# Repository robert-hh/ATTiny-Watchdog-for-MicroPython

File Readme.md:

# ATTiny based Watchdog (for MicroPython devices)

These are two variants of an external watchdog, which I made for use with ES32 based MicroPython
devices. Even if the ESP32 has a built-in watchdog, it is not really reliable. Actually, using
it does not improve the long term reliability of an application.

These two variants consists of two components:

- Software for an AttinyX5 device, which is the actual Watchdog. For (my) convenience
I made it with the Arduino development environment. I selected the ATTiny because it is easy 
available, cheap, well documented, and easy to use and available in various packages. 
Besides the controller and a pull-up resistor for the input, no other component is required.
- A small class for the MicroPython device controlling the watchdog.

These two variants differ on how the communication between the micropython device and
the watchdog is done.

- Pulse: Communication to the watchdog is via one GPIO line and pulses of various duration. 
That is the only drawback of using an external watchdog: it requires an GPIO port for feeding.
- Serial: Communication to the Watchdog is via one GPIO line and serial commands at 9600 baud.
Since only data is sent, I used the RMT module for sending, saving the UART port. For devices
without RMT a UART based variant is supplied.

The run-time overhead of both variants is comparable and differs only in the length of the 
feed pulse. For the **pulse** variant, it is 20µs, for the **serial** and **uart**  variant,
it is 100µs (the length of the start bit at 9600 baud).

Both watchdogs have two states, a sleep state and a watch state. They start in sleep state and have 
to be armed by a dedicated signal. The watch state can be suspended, e.g. before going to deep sleep.
The current consumption of the watchdog is about 1 µA, with short bursts of 1 mA for 500µs every second.

When the watchdog fires (Barks), it creates reset pulse of 100ms duration. For that time, the 
respective GPIO pin of the ATTiny will set to output mode. In all other times, it is in
input mode with pull-up active.

In both version, an Reset signal on the supervized micro is detected and will cause the watchdog 
to enter the sleep state. If the sleep state is timed (see command stop() below), then for that period only.

## Python class

### Serial version, RMT
watchdog = Watchdog(port, status=None, restart=False, baudrate=9600)

**Port** is the name or number of the GPIO port. It is important not to supply a pin
object, but the name, e.g. "P9" or 14. The GPIO pin will be initialized by the class.  
**status** is the name/number of a pin, which, if connected, can be used to read back the 
status of the watchdog. If the status pin is set,   
**restart**=True will cause a feed signal to be sent when status starts toggling,
which is when the watch period is halfway expired. This is useful in situations, when there is no
suitable place for a feed() call. The drawback: feed() is then called in a callback function, which
may even be executed when the to-be-supervized functions stoppped working.
**baudrate** is the speed to be used. The default is 9600 and hardly ever changed.

### Serial version, UART
watchdog = Watchdog(uart, status=None)

**uart** has be be an UART object created with the proper baud rate and pin assignments.  
**status** is a Pin object, defined in input mode for reading back the status pin.

### Pulse version
watchdog = Watchdog(port, status=None, restart=False)

**Port** is the name or number of the GPIO port. It is important not to supply a pin
object, but the name, e.g. "P9" or 14. The GPIO pin will be initialized by the class.  
**status** is the name/number of a pin, which, if connected, can be used to read back 
the status of the watchdog.  
**restart**=True will cause a feed signal to be sent when status starts toggling,
which is when the watch period is halfway expired. This is useful in situations, when there is no
suitable place for a feed() call. The drawback: feed() is then called in a callback function, which
may even be executed when the to-be-supervized functions stoppped working.  

## Methods

### watchdog.start(seconds)

Set the timeout period of the watchdog to seconds and start the watch mode. The granularity is seconds.
The shortest timeout period that can be set in the pulse version is about 15 seconds.

### watchdog.feed()

Feed the dog. The timeout time will be set to the value given by the start() command.
Do not call feed(), e.g. in a different thread, before the start() command terminated, 
which may take a while. After calling feed(), it takes about 2 ms until the status as reported by a
call to status() changes. 

### watchdog.stop(seconds=0)

Suspend the watch state for the given time and enter the sleep state. 
If the value of seconds is not zero, sleep only for that amount of time 
and return to the watch state after that.

### watchdog.status()

Read back the status of the watchdog using the pin set in the constructor. Return values:  

|Value|Meaning|
|:-:|:-|
|0|The watchdog is sleeping|
|1|The watchdog is active. If the watch period is halfway elapsed, the value gets togggling once per second. That can be used for instance to trigger a callback, which feeds the watchdog.|
|None|Port no set|

### watchdog.send(string)

Send string to the watchdog device using the baud rate set in the constructor. 
That is the basic command used by the methods start() and stop(). 
You can use that to toggle DEBUG output from the watchdog, by calling send("D").
In the pulse version, send() exists but does not do anything.

## Command interface of the ATTiny

### Pin assignments of the Attiny:

|Pin|Port|Function|
|:-:|:-:|:-|
|2|PB3|Reset signal to host (required)|
|3|PB4|Feed and command input pin (recommended)|
|4|GND|GND (required)|
|6|PB1|Status pin (optional)|
|7|PB2|Debug output pin. (optional)|
|8|Vcc|3.3 - 5V Vcc (required)|

### Serial interface

The following commands are supported: 

| Command | Description |
|:-:|:--|
|Snnn|Set the timeout of the watchdog and change to the watch state. nnn is the value in seconds. The command can be repeated while in watch state and will set a new timeout.|
|Pnnn|Suspend the watch state and return to the sleep state. If the number nnn is given and > 0, then sleep for that time only and return to the watch state after that.|
|Dn|n is a number, which may be omitted. If the value is 0, toggle the DEBUG output. If the value is not 0, switch DEBUG ouput on. The output is send to Port PB2 of the ATTiny with 9600 baud.|
|anything else|Feed the dog. For speed, the feed command actually only creates a start bit, and the ATTiny then reads 0xff as character.|

The DEBUG output of the ATTiny will echo the command and countdown the time in watch mode.  
The status output will indicate the watchdog state; low for sleeping and high for watching.

For the serial version a pull-up resistor at the communication link is highly recommended. The serial 
interface in the ATTiny uses the SoftSerial module of Arduino. It depends on the internal clock of 
the ATTiny (1 MHz here), which is not 100% accurate. In my test, the clock speed was 
about 1.005 MHz +/- 2 KHz. For asynchronous serial, that is still within the tolerated error range.

### Pulse interface

The following pulse time ranges are defined: 

|State| Duration| Description |
|:-:|:-:|:--|
|sleep|pulse < 5 ms|Feed pulse. Will be ignored|
|sleep|5 ms <= pulse < 10 ms|Stay in sleep mode. If after less than 10 ms it is followed by another pulse, that time is taken as sleep timeout.|
|sleep|10 ms <= pulse < 3600 ms|Set the timeout of the watchdog and change to the watch state. The pulse duration in ms defines the timeout value in seconds.|
|watch|20 µs < pulse < 5 ms|Feed the dog.| 
|watch|5 ms <= pulse < 10 ms|Suspend the watch state and enter the sleep state. If after less than 10 ms it is followed by another pulse, the length of that pulse is taken as sleep timeout.|
|watch|10 ms <= pulse < 3600 ms|Restart the watch state and set the new timeout.|

Pulses longer that 3600ms will be ignored in both states. That covers a line which is permanently low. The determination of the pulse duration is not very accurate, but good enough for the purpose.

The debug output will respond to the input with a series of pulses.   
- The first pulse length shows, if a internal timeout (~200µs) or a signal from the host (~1 ms) happened.   
- The second pulse shows the state of the watchdog, short for sleep and long for watch.   
- The third pulse shows the state of the reset line, short for high and long for low.  
- That is followed  by a burst of short pulses. The burst length indicates the remaining time until
timeout in the respective state. 

The status output will indicate the watchdog state; low for sleeping and high for watching.

## Example

Basic example:

```
import watchdog

wd = watchdog.Watchdog("P9")
wd.start(100) # set a timeout of 100 seconds and start
#
# To feed, call regularly
#
wd.feed()
#
# to stop, call
#
wd.stop()
```

Basic example using the internal callback for feeding:

```
import watchdog

wd = watchdog.Watchdog("P9", "P10", True)
wd.start(100) # set a timeout of 100 seconds and start
#
# No explicit call to feed is required
#
# to stop, call
#
wd.stop()
```

UART example using an dedicated callback for feeding:

```
import watchdog
from machine import UART, Pin

uart=UART(1, 9600)
pin = Pin("P10", Pin.IN)
wd = watchdog_uart.Watchdog(uart, pin)
pin.callback(Pin.IRQ_FALLING, handler=lambda p: wd.feed())

wd.start(100) # set a timeout of 100 seconds and start
#
# No explicit call to feed is required
#
# to stop, call
#
wd.stop()
```

## License

The MIT License (MIT)

Copyright (c) 2021 RobertHammelrath

Permission is hereby granted, free of charge, to any person obtaining a copy
of this software and associated documentation files (the "Software"), to deal
in the Software without restriction, including without limitation the rights
to use, copy, modify, merge, publish, distribute, sublicense, and/or sell
copies of the Software, and to permit persons to whom the Software is
furnished to do so, subject to the following conditions:
The above copyright notice and this permission notice shall be included in
all copies or substantial portions of the Software.

THE SOFTWARE IS PROVIDED "AS IS", WITHOUT WARRANTY OF ANY KIND, EXPRESS OR
IMPLIED, INCLUDING BUT NOT LIMITED TO THE WARRANTIES OF MERCHANTABILITY,
FITNESS FOR A PARTICULAR PURPOSE AND NONINFRINGEMENT. IN NO EVENT SHALL THE
AUTHORS OR COPYRIGHT HOLDERS BE LIABLE FOR ANY CLAIM, DAMAGES OR OTHER
LIABILITY, WHETHER IN AN ACTION OF CONTRACT, TORT OR OTHERWISE, ARISING FROM,
OUT OF OR IN CONNECTION WITH THE SOFTWARE OR THE USE OR OTHER DEALINGS IN
THE SOFTWARE.

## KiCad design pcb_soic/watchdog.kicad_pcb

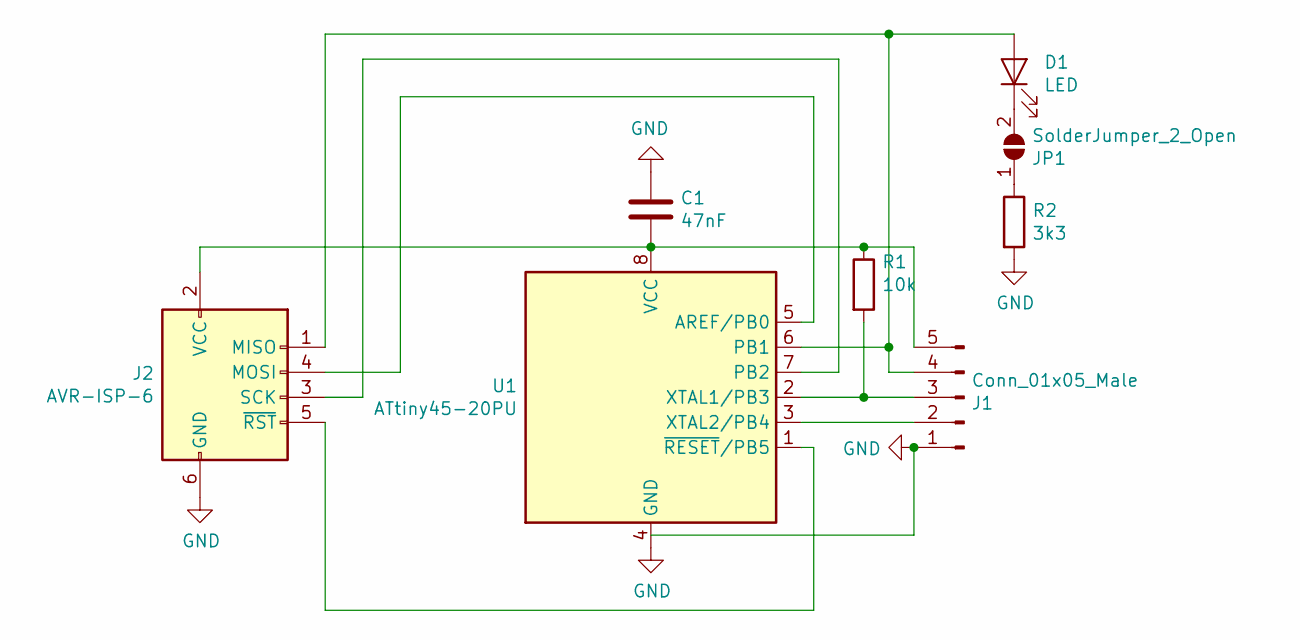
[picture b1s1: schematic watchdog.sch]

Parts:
C1: 47nF; C_1206_3216Metric_Pad1.42x1.75mm_HandSolder
D1: LED; LED_1206_3216Metric_Pad1.42x1.75mm_HandSolder
J1: Conn_01x05_Male; PinHeader_1x05_P2.54mm_Vertical
J2: AVR-ISP-6; PinHeader_2x03_P2.54mm_Vertical
JP1: SolderJumper_2_Open; SolderJumper-2_P1.3mm_Open_TrianglePad1.0x1.5mm
R1: 10k; R_1206_3216Metric_Pad1.42x1.75mm_HandSolder
R2: 3k3; R_1206_3216Metric_Pad1.42x1.75mm_HandSolder
U1: ATtiny45-20PU; DIP-8_W7.62mm

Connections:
GND: C1.1, J1.1, J2.6 (GND), R2.2, U1.4 (GND)
unnamed: C1.2, J1.5, J2.2 (VCC), R1.1, U1.8 (VCC)
unnamed: D1.1 (K), JP1.2 (B)
unnamed: D1.2 (A), J1.4, J2.1 (MISO), U1.6 (PB1)
unnamed: J1.2, U1.3 (XTAL2/PB4)
unnamed: J1.3, R1.2, U1.2 (XTAL1/PB3)
unnamed: J2.3 (SCK), U1.7 (PB2)
unnamed: J2.4 (MOSI), U1.5 (AREF/PB0)
unnamed: J2.5 (~RST), U1.1 (~RESET~/PB5)
unnamed: JP1.1 (A), R2.1

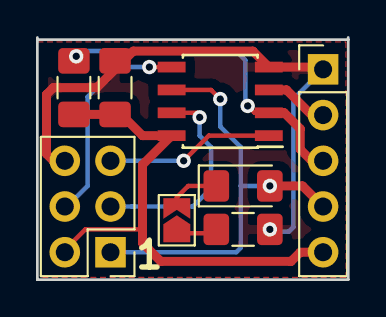
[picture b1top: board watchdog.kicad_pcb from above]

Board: 2 copper layers, 17.3 x 13.5 mm, 8 parts (0 on the bottom side), 10 nets.

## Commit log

2019-11-28 Watchdog: Two versions of an ATTinyx5 based watchdog timer
    For instance to be used in combination with MicroPython devices.
2019-11-28 Readme.md: Add an example
2019-11-28 watchdog.ino: Remove unused code lines
2019-11-28 watchdog.ino: Change the logic of the pulse variant
    The behaviour is the same in both states:
    - seting a timeout will always do so and go into the watch state
    - suspend will always lead to a sleeping state
    As a consequence, the smallest timeout is now about 10 seconds.
2019-11-29 watchdog.ino: Make the pulse variant restartable
    In both states, suspend switched to sleep() mode and set() starts or
    restarts the timer.
    Other changes:
    - A status method for the pulse variant.
    - A watchdog_uart.py variant for the serial interface, which uses
    a uart instead of the RMT module fpr communication.
2019-11-29 serial/watchdog.py: Fix glitch
    Additional: add dummy status() method to match the pulse variant.
2019-11-30 watchdog.py: Change the method names to more obvious ones
    set() -> start()
    suspend() -> stop()
2019-11-30 pcv/*: A Kicad Layout for a small board
    In cased that it is to be added to an existing set-up, I sketched this
    board. All with big component for hand soldering. It has a AVR-ISP
    connecro area too, which take 30% of the board.
2019-11-30 watchdog: Major rework
    serial variant: Support now the status() command
    both variants: Detect a manual reset on the reset line and stop
    the watchdog. Assuming it will be re-started after devuce start-up.
2019-11-30 Readme.md: Update the documentation
2019-11-30 pcb: small change to the PCB
2019-12-01 watchdog: Rework and cleaning
    pulse/watchdog.py:
    - add the dummy argument to stop(), and make send() cause a feed signal
    pulse/watchdog/watchdog.ino:
    - clean up the code. Remove unused variables
    serial/watchdog.py:
    serial/watchdog_uart.py:
2019-12-02 watchdog: Major rework of the Arduino files
    Both files now are mostly similar, with the exception of the interface
    handling. The timed sleep method was also added to the pulse version.
    The documentation was changed and extended to reflect the code change.
2019-12-03 watchdog: Added the compiled HEX files
2019-12-05 watchdog/pulse: Change method for timing the pulse
    Instead of counting delays, micros() is used to time
    the command pulse.
    Also: change the method in pyboard.py to create the command pulse,
    since utime.sleep_ms() has too much jitter; it is: time -1/+0.5 ms.
    Using consecutive calls of utime.sleep_us(950) give better results.
2019-12-05 watchdog.ino: Swapped pin 3 and 4
    I had a bug in my PCB and already made samples, and it is easier to
    change the code than the PCB. At least just now.
2019-12-06 watchdog.py, pulse variant: Fore a minimal watch time
    Otherwise, a start() signal looks like a stop() signal.
    Also: Minor change on the PCB. Add a label and make the board
    just a little bit smaller by narrowing the edges.
2019-12-06 Readme.md: Update, clarification and typo fix.
2019-12-08 watchdog files: Toggle status after halfway through the watch time
    That will support to find the proper time to refeed, and also
    to feed via a callback function. Support for the latter is built
    into two of the watchdog.py stubs.
    The documentation is extended accordingly, with additional examples.
2019-12-20 serial/watchdog.py: Simplify the code
    by using RMT for the feed signal too.
2019-12-20 pcb: Change layout.
    Rotate Attiny by 90°
2019-12-20 pcb_soic: Add smaller PCB with SMD components
    Large components are used, such that hand soldering is still possible.
    A LED was added to the board too showing the state (if required).
    The size of the PCB is now 13x17mm (was 14x20mm before). Most of the
    space is used by the connectors.
2020-01-13 serial/watchdog*: Add RMT variant for the mp.org version
    Also:
    Rename the serial/watchdog.py version
2021-06-06 watchdog: Add the MIT License header to all files.
2021-07-29 Watchog Pulse: Swap Reset and Feed pin numbers.
    That neede to be changed matching the sample PCB layout. Thanks to
    User @l0j0 for notifying.
